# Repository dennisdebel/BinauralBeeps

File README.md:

# BinauralBeeps
Insructions and files to build a (binaural) elecromagnetic spectrum sonifier (also known as an EM Sniffer). Including LEDS for long exposure photography visualising the EM fields. 

### Todo
* Add IMU to digitally process EM field data for visualisation.

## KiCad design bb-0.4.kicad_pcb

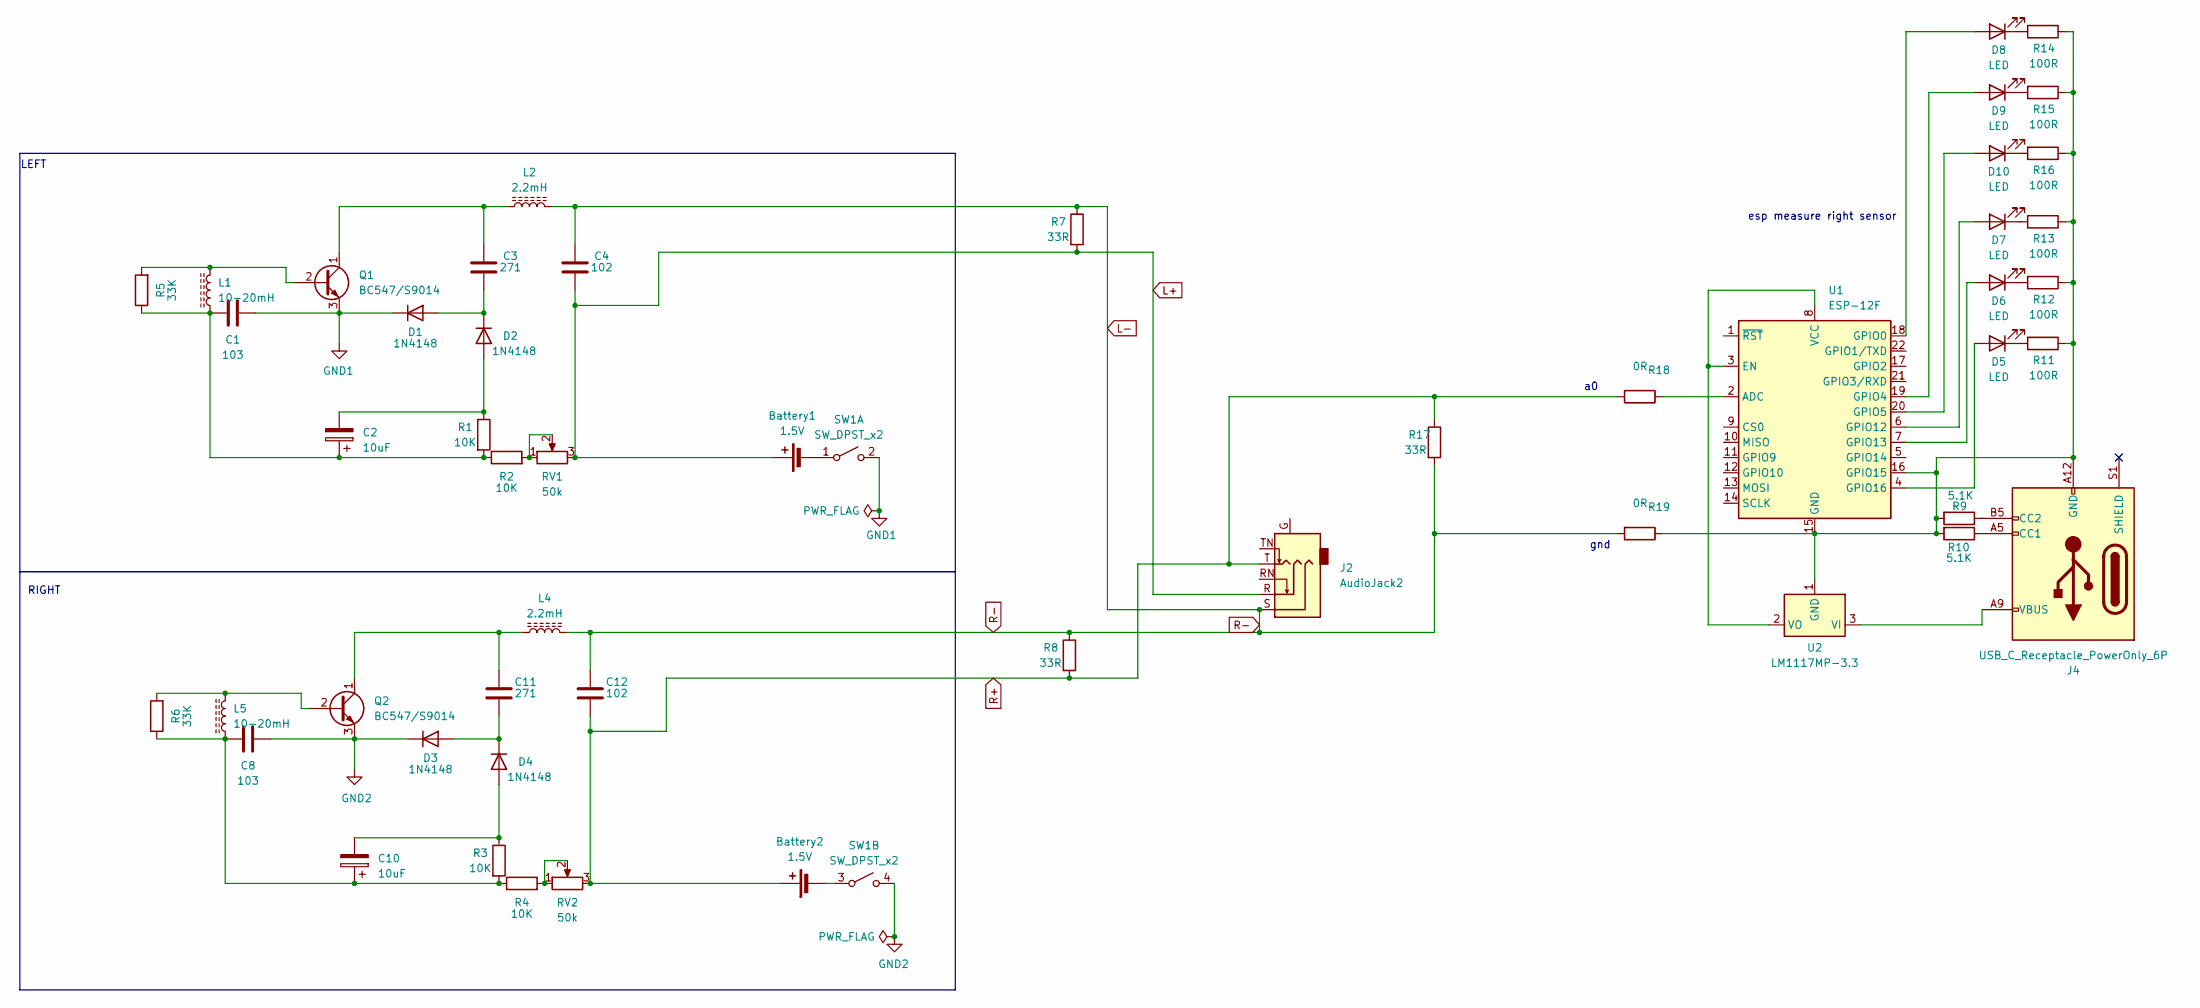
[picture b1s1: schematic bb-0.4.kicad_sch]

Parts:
Battery1, Battery2: 1.5V; BatteryHolder_Keystone_2460_1xAA
C1, C8: 103; C_Disc_D4.3mm_W1.9mm_P5.00mm
C2, C10: 10uF; CP_Radial_D5.0mm_P2.50mm
C3, C11: 271; C_Disc_D4.3mm_W1.9mm_P5.00mm
C4, C12: 102; C_Disc_D4.3mm_W1.9mm_P5.00mm
D1, D2, D3, D4: 1N4148; D_DO-35_SOD27_P7.62mm_Horizontal
D5, D6, D7, D8, D9, D10: LED; LED_D5.0mm
J2: AudioJack2; Jack_3.5mm_CUI_SJ1-3525N_Horizontal
J4: USB_C_Receptacle_PowerOnly_6P; USB_C_Receptacle_HRO_TYPE-C-31-M-17
L1, L5: 10-20mH; LairdTech_28C0236-0JW-10
L2, L4: 2.2mH; LairdTech_28C0236-0JW-10
Q1, Q2: BC547/S9014; TO-92_Inline_Wide
R1, R2, R3, R4: 10K; R_Axial_DIN0207_L6.3mm_D2.5mm_P10.16mm_Horizontal
R5, R6: 33K; R_Axial_DIN0207_L6.3mm_D2.5mm_P10.16mm_Horizontal
R7, R8, R17: 33R; R_Axial_DIN0207_L6.3mm_D2.5mm_P10.16mm_Horizontal
R9, R10: 5.1K; R_Axial_DIN0207_L6.3mm_D2.5mm_P10.16mm_Horizontal
R11, R12, R13, R14, R15, R16: 100R; R_Axial_DIN0207_L6.3mm_D2.5mm_P10.16mm_Horizontal
R18, R19: 0R; R_Axial_DIN0207_L6.3mm_D2.5mm_P10.16mm_Horizontal
RV1, RV2: 50k; Potentiometer_Runtron_RM-065_Vertical
SW1: SW_DPST_x2; SW_Push_2P1T_Toggle_CK_PVA1xxH1xxxxxxV2
U1: ESP-12F; ESP-12E
U2: LM1117MP-3.3; SOT-223-3_TabPin2

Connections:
GND1: C1.1, D1.1 (K), Q1.3 (E), SW1.2 (B)
GND2: C8.1, D3.1 (K), Q2.3 (E), SW1.4 (B)
L+: Battery1.1 (+), C4.1, J2.R, R7.2, RV1.3
L-: C4.2, C12.2, J2.S, L2.2, L4.2, R7.1, R8.1, R17.2, R19.2
unnamed: Battery1.2 (-), SW1.1 (A)
unnamed: Battery2.2 (-), SW1.3 (A)
unnamed: C1.2, C2.1, L1.1, R1.2, R2.1, R5.1
unnamed: C8.2, C10.1, L5.1, R3.2, R4.1, R6.1
unnamed: C3.1, D1.2 (A), D2.1 (K)
unnamed: C2.2, D2.2 (A), R1.1
unnamed: C11.1, D3.2 (A), D4.1 (K)
unnamed: C10.2, D4.2 (A), R3.1
unnamed: D5.2 (A), U1.4 (GPIO16)
unnamed: D5.1 (K), R11.2
unnamed: D6.2 (A), U1.7 (GPIO13)
unnamed: D6.1 (K), R12.2
unnamed: D7.2 (A), U1.6 (GPIO12)
unnamed: D7.1 (K), R13.2
unnamed: D8.2 (A), U1.18 (GPIO0)
unnamed: D8.1 (K), R14.2
unnamed: D9.2 (A), U1.19 (GPIO4)
unnamed: D9.1 (K), R15.2
unnamed: D10.2 (A), U1.20 (GPIO5)
unnamed: D10.1 (K), R16.2
unnamed: J4.A5 (CC1), R10.1
unnamed: J4.B5 (CC2), R9.1
unnamed: L1.2, Q1.2 (B), R5.2
unnamed: C3.2, L2.1, Q1.1 (C)
unnamed: L5.2, Q2.2 (B), R6.2
unnamed: C11.2, L4.1, Q2.1 (C)
unnamed: R2.2, RV1.1, RV1.2
unnamed: R4.2, RV2.1, RV2.2
unnamed: R18.1, U1.2 (ADC)
unnamed: U1.3 (EN), U1.8 (VCC), U2.2 (VO)
unnamed: J4.A12 (GND), J4.B12 (GND), R9.2, R10.2, R11.1, R12.1, R13.1, R14.1, R15.1, R16.1, R19.1, U1.15 (GND), U1.16 (GPIO15), U2.1 (GND)
unnamed: J4.A9 (VBUS), J4.B9 (VBUS), U2.3 (VI)
R+: Battery2.1 (+), C12.1, J2.T, R8.2, R17.1, R18.2, RV2.3

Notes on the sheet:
RIGHT
esp measure right sensor
LEFT
gnd

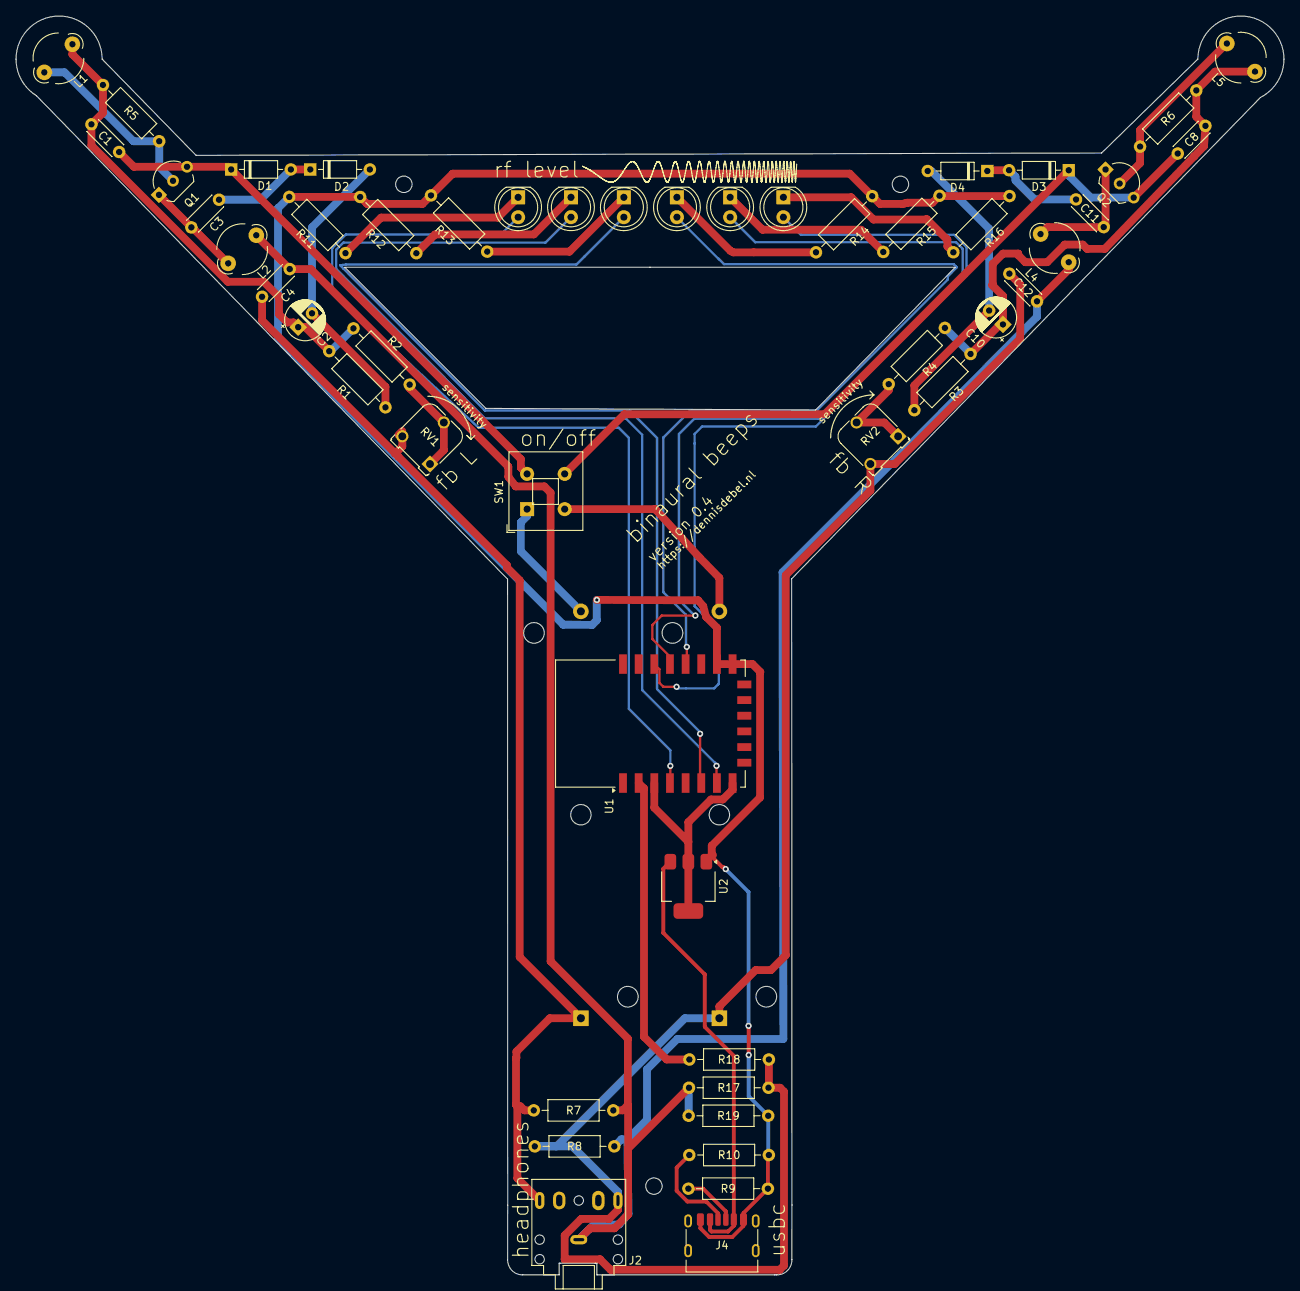
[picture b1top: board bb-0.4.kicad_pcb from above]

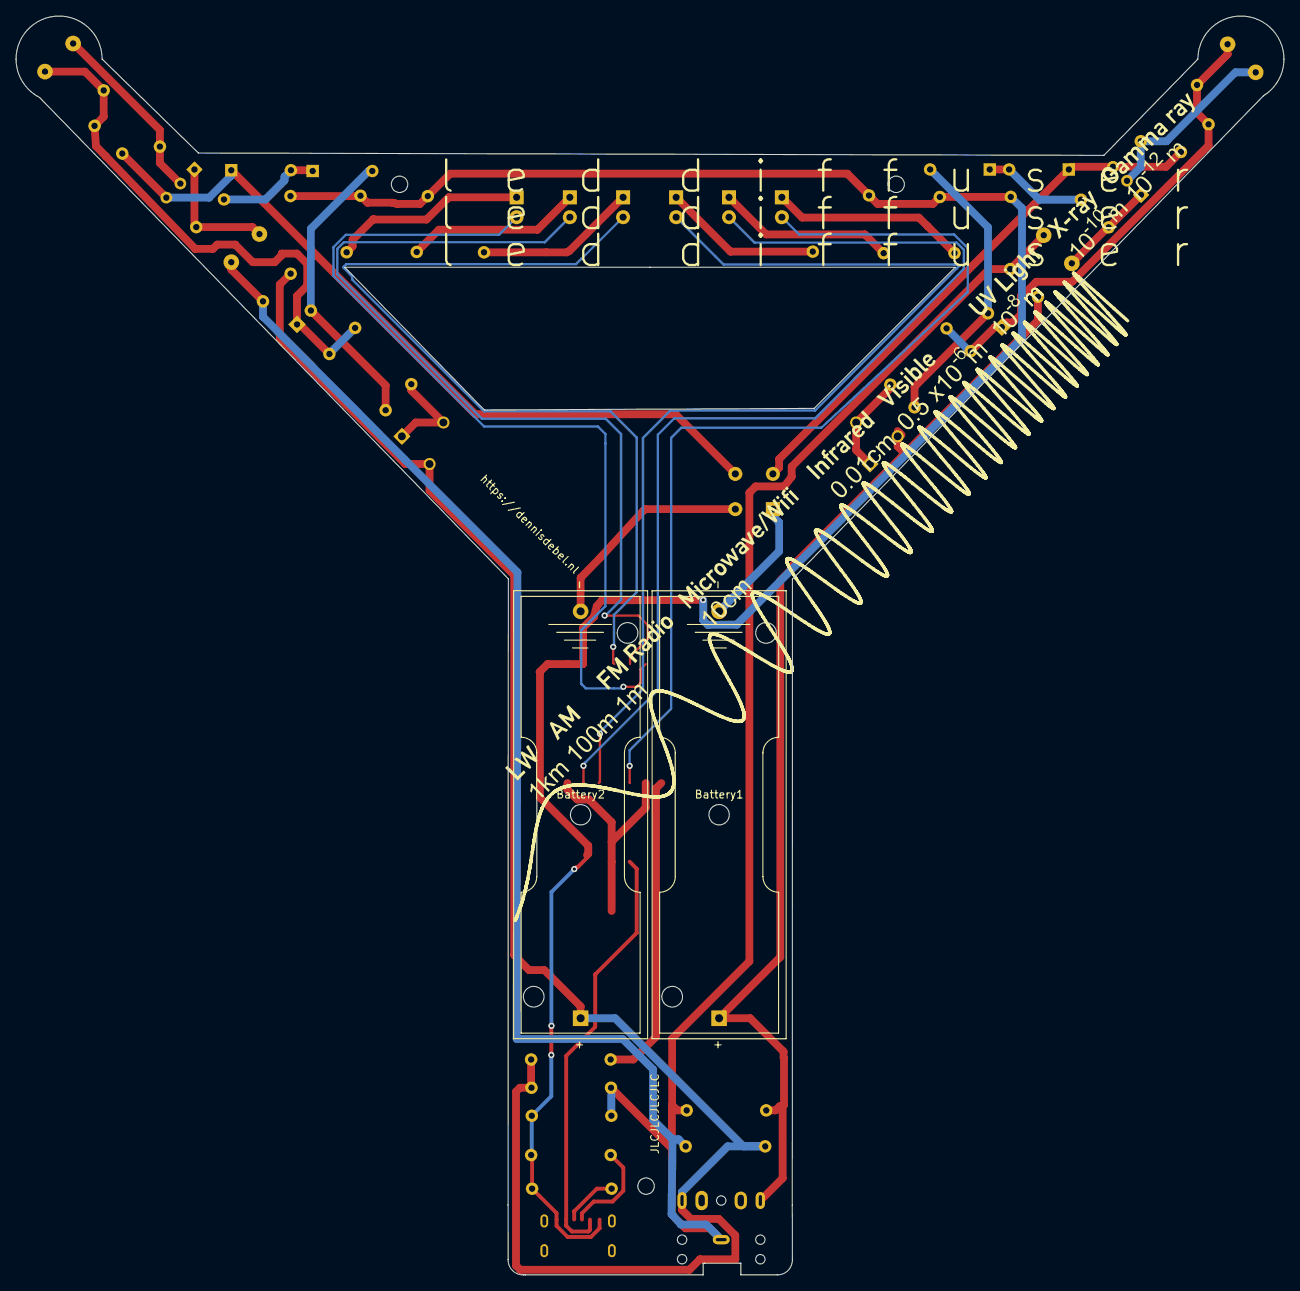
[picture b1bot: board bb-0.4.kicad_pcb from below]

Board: 2 copper layers, 162.0 x 160.8 mm, 52 parts (2 on the bottom side), 37 nets.

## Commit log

2024-12-19 First commit, not very useful, come back later
2025-01-04 Adding deisgn files for stereo (binaural version)
2025-02-01 Added version 0.1
    Waiting for parts, design is untested (and needs some changes like a mounting hole in the bottom part)
2025-02-05 updated to version 0.2
2025-02-05 new gerbers (silk screen adjustment)
2025-02-06 removed old gerbers
2025-02-06 Version 0.3
    ESP ground bodge fix
2025-02-06 added annotion ground issue
2025-02-06 typo
2025-02-07 hotfix: A0 cut by hole
2025-02-07 added 0.3 gerbers
2025-02-11 added version 0.4 files
